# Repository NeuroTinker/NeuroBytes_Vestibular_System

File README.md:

# NeuroBytes Vestibular System
NeuroBytes are open-source hardware neuron simulators designed and sold by [NeuroTinker, LLC](http://www.neurotinker.com/). The Vestibular System boards emulate the portion of the inner ear responsible for orientation.  

All NeuroBytes products are based on the ST32L0x series of ARM Cortex-M0+ 32-bit microcontrollers. The boards were designed in KiCad and Inkscape and are released under the terms of the GPL, v3.0.

This repository is a continuation of the 8-bit ATtiny design called [NeuroBytes v0.91](https://github.com/zakqwy/neurobytes). The two series are not compatible.

## Project Status
This project is in alpha. The firmware is in progress and the API may change at any time. The PCB design is physically tested but has not yet been manufactured at scale.

## More Information
The NeuroBytes GitHub repositories store engineering information and make the design history of the project available to the public. Hardware- and firmware-specific README.md files can be found in their appropriate subdirectories. 

We encourage community involvement in our efforts, keeping in mind that hardware availability is currently quite limited. For product availability, operating guidelines, curricula, and information about NeuroTinker, LLC, head to neurotinker.com. Further technical logs are also at https://hackaday.io/project/3339-neurobytes.

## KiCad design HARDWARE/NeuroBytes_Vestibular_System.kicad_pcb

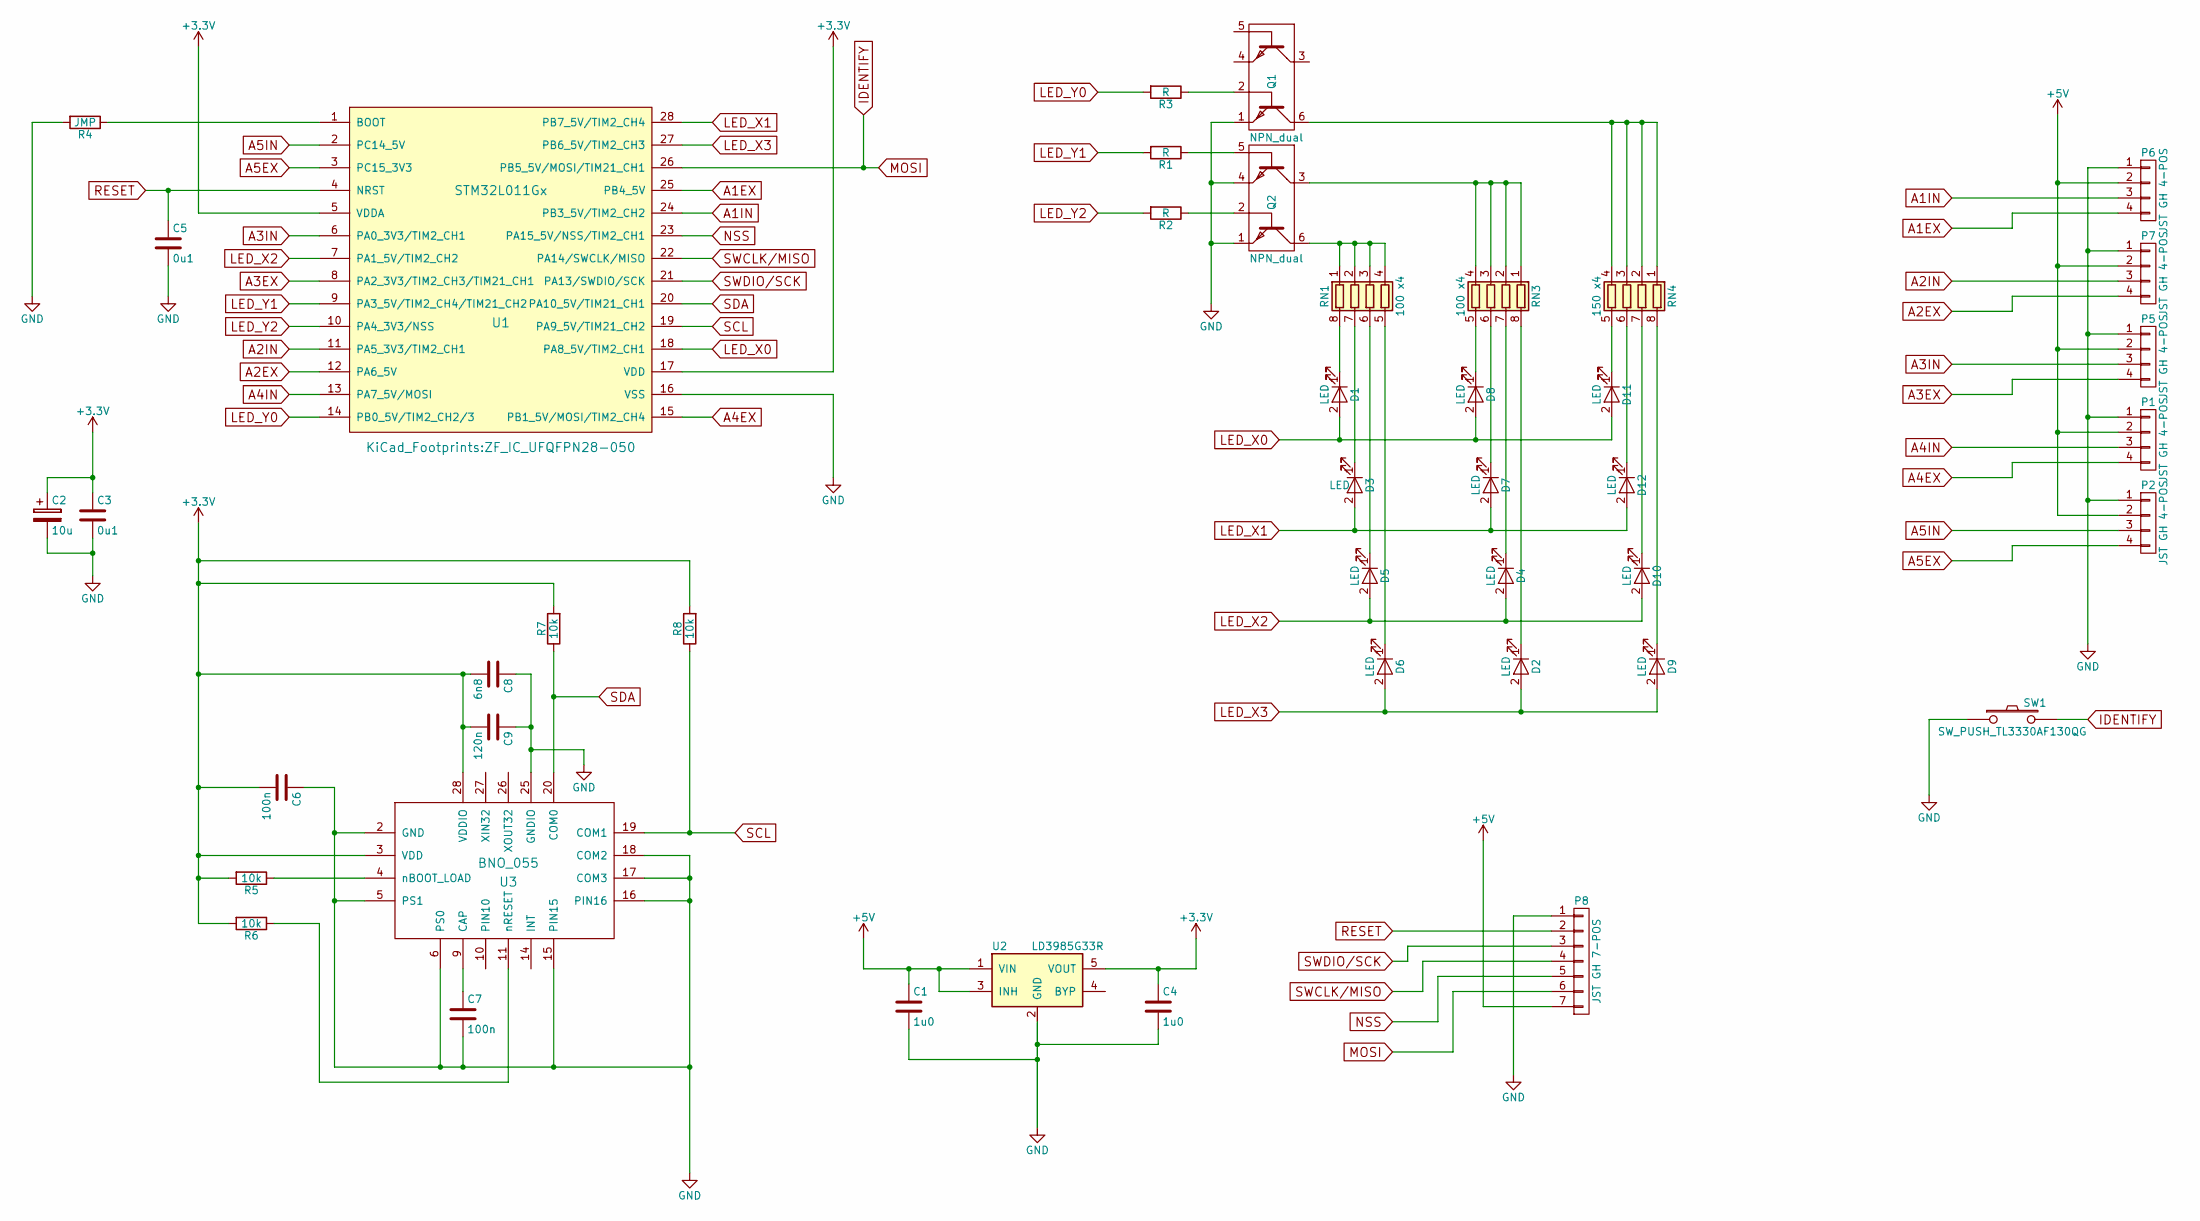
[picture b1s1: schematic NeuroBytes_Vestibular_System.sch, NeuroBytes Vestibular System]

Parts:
C1, C4: 1u0; ZF_SMD_NonPol_0603
C2: 10u; ZF_SMD_pol_1206
C3, C5: 0u1; ZF_SMD_NonPol_0402_cap
C6, C7: 100n; ZF_SMD_NonPol_0402_cap
C8: 6n8; ZF_SMD_NonPol_0402_cap
C9: 120n; ZF_SMD_NonPol_0402_cap
D1, D2, D3, D4, D5, D6, D7, D8, D9, D10, D11, D12: LED; ZF_SMD_NonPol_0402
P1, P2, P5, P6, P7: JST GH 4-POS; ZF_CONN_JST_GH
P8: JST GH 7-POS; ZF_CONN_JST_GH_7POS
Q1, Q2: NPN_dual; ZF_SMD_SOT-363
R1, R2, R3: R; ZF_SMD_NonPol_0402
R4: JMP; ZF_SMD_NonPol_0402
R5, R6, R7, R8: 10k; ZF_SMD_NonPol_0402
RN1, RN3: 100 x4; ZF_RN_4iso_CTS-0804
RN4: 150 x4; ZF_RN_4iso_CTS-0804
SW1: SW_PUSH_TL3330AF130QG; ZF_SW_Momentary_SideMtg
U1: STM32L011Gx; ZF_IC_UFQFPN28-050
U2: LD3985G33R; ZF_SOT23-5L
U3: BNO_055; ZF_IC_28LGA

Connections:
+3V3: C2.1, C3.1, C4.1, C6.2, C8.2, C9.2, R5.2, R6.2, R7.2, R8.2, U1.5 (VDDA), U1.17 (VDD), U2.5 (VOUT), U3.3 (VDD), U3.28 (VDDIO)
+5V: C1.1, P1.2, P2.2, P5.2, P6.2, P7.2, P8.7, U2.1 (VIN), U2.3 (INH)
A1EX: P6.4, U1.25 (PB4_5V)
A1IN: P6.3, U1.24 (PB3_5V/TIM2_CH2)
A2EX: P7.4, U1.12 (PA6_5V)
A2IN: P7.3, U1.11 (PA5_3V3/TIM2_CH1)
A3EX: P5.4, U1.8 (PA2_3V3/TIM2_CH3/TIM21_CH1)
A3IN: P5.3, U1.6 (PA0_3V3/TIM2_CH1)
A4EX: P1.4, U1.15 (PB1_5V/MOSI/TIM2_CH4)
A4IN: P1.3, U1.13 (PA7_5V/MOSI)
A5EX: P2.4, U1.3 (PC15_3V3)
A5IN: P2.3, U1.2 (PC14_5V)
GND: C1.2, C2.2, C3.2, C4.2, C5.2, C6.1, C7.2, C8.1, C9.1, P1.1, P2.1, P5.1, P6.1, P7.1, P8.1, Q1.1, Q2.1, Q2.4, R4.2, SW1.1, U1.16 (VSS), U2.2 (GND), U3.2 (GND), U3.5 (PS1), U3.6 (PS0), U3.15 (PIN15), U3.16 (PIN16), U3.17 (COM3), U3.18 (COM2), U3.25 (GNDIO)
IDENTIFY: P8.6, SW1.2, U1.26 (PB5_5V/MOSI/TIM21_CH1)
LED_X0: D1.2 (A), D8.2 (A), D11.2 (A), U1.18 (PA8_5V/TIM2_CH1)
LED_X1: D3.2 (A), D7.2 (A), D12.2 (A), U1.28 (PB7_5V/TIM2_CH4)
LED_X2: D4.2 (A), D5.2 (A), D10.2 (A), U1.7 (PA1_5V/TIM2_CH2)
LED_X3: D2.2 (A), D6.2 (A), D9.2 (A), U1.27 (PB6_5V/TIM2_CH3)
LED_Y0: R3.2, U1.14 (PB0_5V/TIM2_CH2/3)
LED_Y1: R1.2, U1.9 (PA3_5V/TIM2_CH4/TIM21_CH2)
LED_Y2: R2.2, U1.10 (PA4_3V3/NSS)
NSS: P8.5, U1.23 (PA15_5V/NSS/TIM2_CH1)
unnamed: C7.1, U3.9 (CAP)
unnamed: D1.1 (K), RN1.8 (R1.2)
unnamed: D2.1 (K), RN3.8 (R1.2)
unnamed: D3.1 (K), RN1.7 (R2.2)
unnamed: D4.1 (K), RN3.7 (R2.2)
unnamed: D5.1 (K), RN1.6 (R3.2)
unnamed: D6.1 (K), RN1.5 (R4.2)
unnamed: D7.1 (K), RN3.6 (R3.2)
unnamed: D8.1 (K), RN3.5 (R4.2)
unnamed: D9.1 (K), RN4.8 (R1.2)
unnamed: D10.1 (K), RN4.7 (R2.2)
unnamed: D11.1 (K), RN4.5 (R4.2)
unnamed: D12.1 (K), RN4.6 (R3.2)
unnamed: Q1.2 (BASE2), R3.1
unnamed: Q1.6, RN4.1 (R1.1), RN4.2 (R2.1), RN4.3 (R3.1), RN4.4 (R4.1)
unnamed: Q2.2 (BASE2), R2.1
unnamed: Q2.3, RN3.1 (R1.1), RN3.2 (R2.1), RN3.3 (R3.1), RN3.4 (R4.1)
unnamed: Q2.5 (BASE1), R1.1
unnamed: Q2.6, RN1.1 (R1.1), RN1.2 (R2.1), RN1.3 (R3.1), RN1.4 (R4.1)
unnamed: R4.1, U1.1 (BOOT)
unnamed: R5.1, U3.4 (nBOOT_LOAD)
unnamed: R6.1, U3.11 (nRESET)
RESET: C5.1, P8.2, U1.4 (NRST)
SCL: R8.1, U1.19 (PA9_5V/TIM21_CH2), U3.19 (COM1)
SDA: R7.1, U1.20 (PA10_5V/TIM21_CH1), U3.20 (COM0)
SWCLK/MISO: P8.4, U1.22 (PA14/SWCLK/MISO)
SWDIO/SCK: P8.3, U1.21 (PA13/SWDIO/SCK)

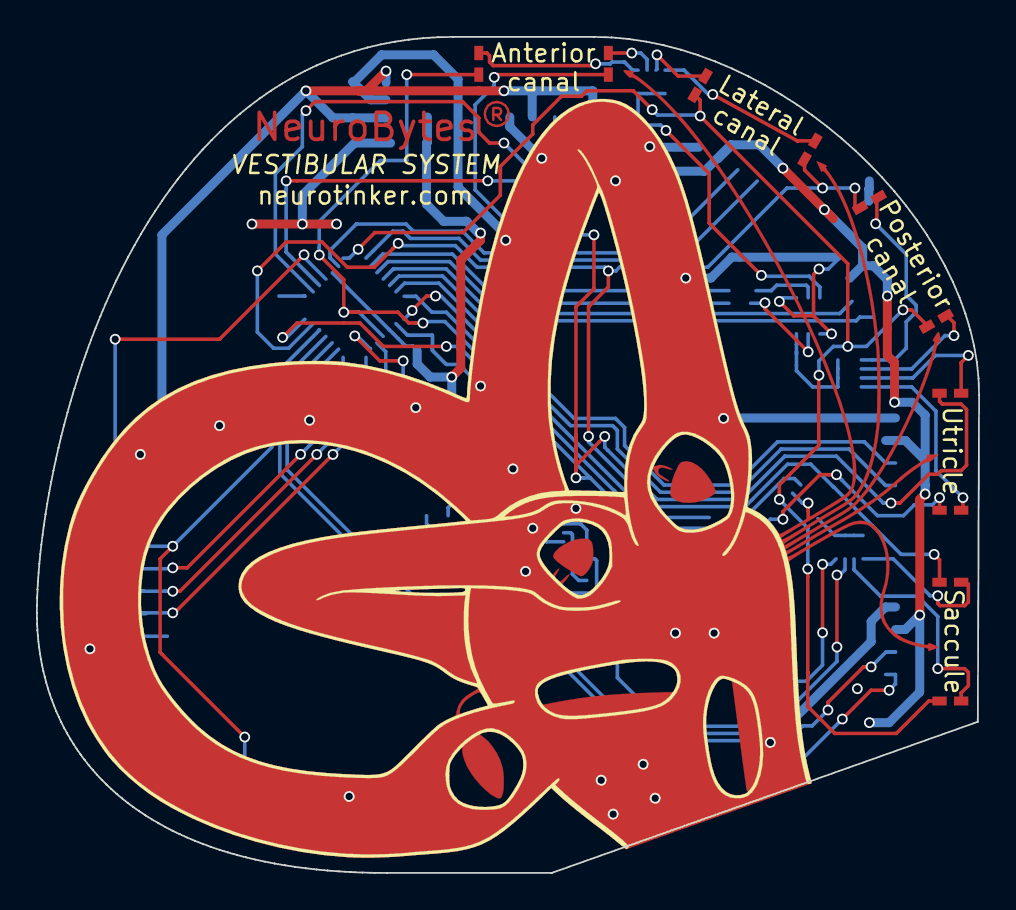
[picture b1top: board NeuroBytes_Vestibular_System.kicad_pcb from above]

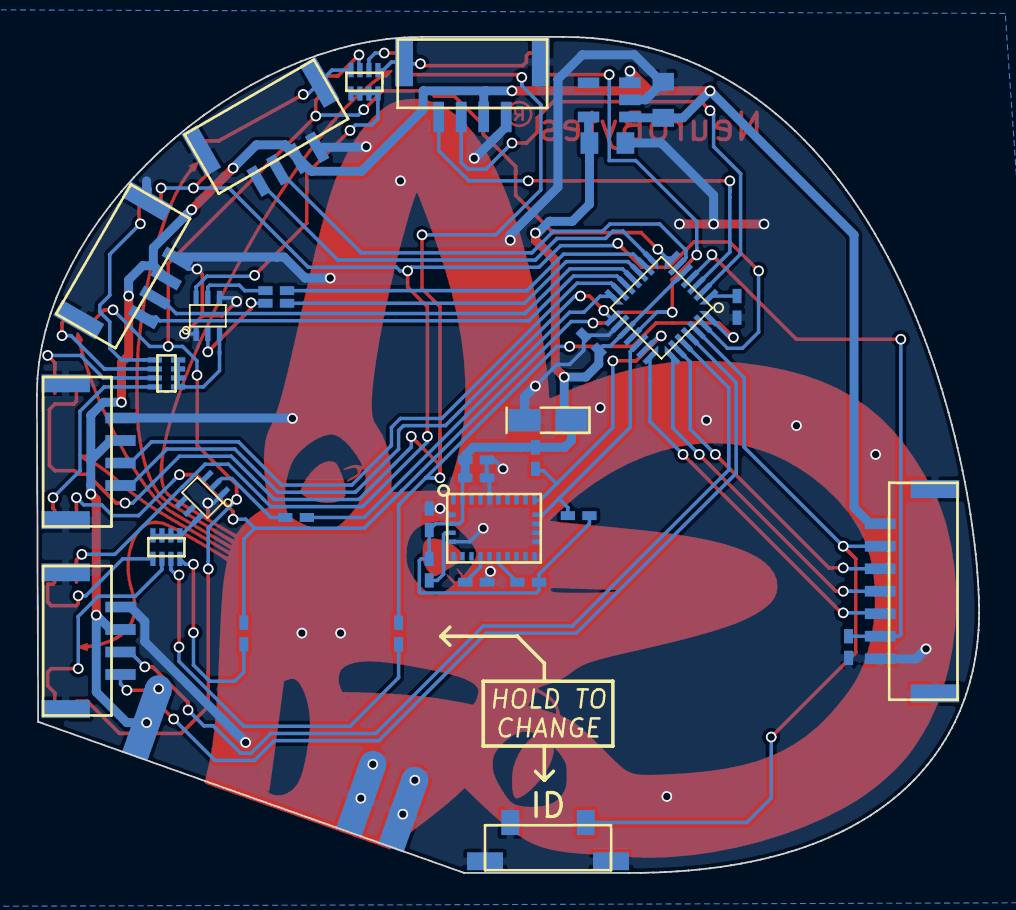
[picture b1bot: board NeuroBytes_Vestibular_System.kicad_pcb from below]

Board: 2 copper layers, 52.3 x 46.4 mm, 44 parts (34 on the bottom side), 49 nets.

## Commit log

2017-05-28 Initial commit. Made BNO055 schematic symbol and footprint. First draft of schematic. Grouped components on PCB. No artwork or routing yet.
2017-06-15 Updated graphics to improve 3D orthoganol canal effect.
2017-06-16 first PCB routing revision.
2017-06-27 minor PCB updates. generated paste gerber for stencil.
2017-06-27 added license and readme
2017-06-27 reversed LEDs
2017-06-28 First firmware test with BNO055 and multiplexed LEDs. No left/right switching, acceleration (utricle/saccule), comms, or NB output functions.
2017-06-28 swapped lateral and posterior canals. started testing accelerometer. pushed led matrix stuff to ISR. increased pwm frequency. regenerated gamma table.
2017-07-04 added linear acceleration

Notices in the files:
HARDWARE/NeuroBytes_Vestibular_System.sch:
License: GPL v3
